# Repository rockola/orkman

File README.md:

# Orkman

[Runoffgroove Mockman](http://www.runoffgroove.com/mockman.html)

* v0.1 - 2020-04-08: initial version

## Description

From http://www.runoffgroove.com/mockman.html :

This circuit sounds uncannily reminiscent of the Rockman units from
the 1980s, minus the compression. Distortion is created by overdriving
the op-amps, similar to the Sansamp units. Adding the optional Red
LEDs will result in an even closer copy of the Rockman sound. When
including the LEDs, reduce the 470k resistors to avoid
over-distorting. You can also increase the 10k resistor for less
overdrive.

## License 

Mockman by runoffgroove.com is licensed under a Creative Commons
Attribution-NonCommercial-ShareAlike 3.0 Unported License.

## Images

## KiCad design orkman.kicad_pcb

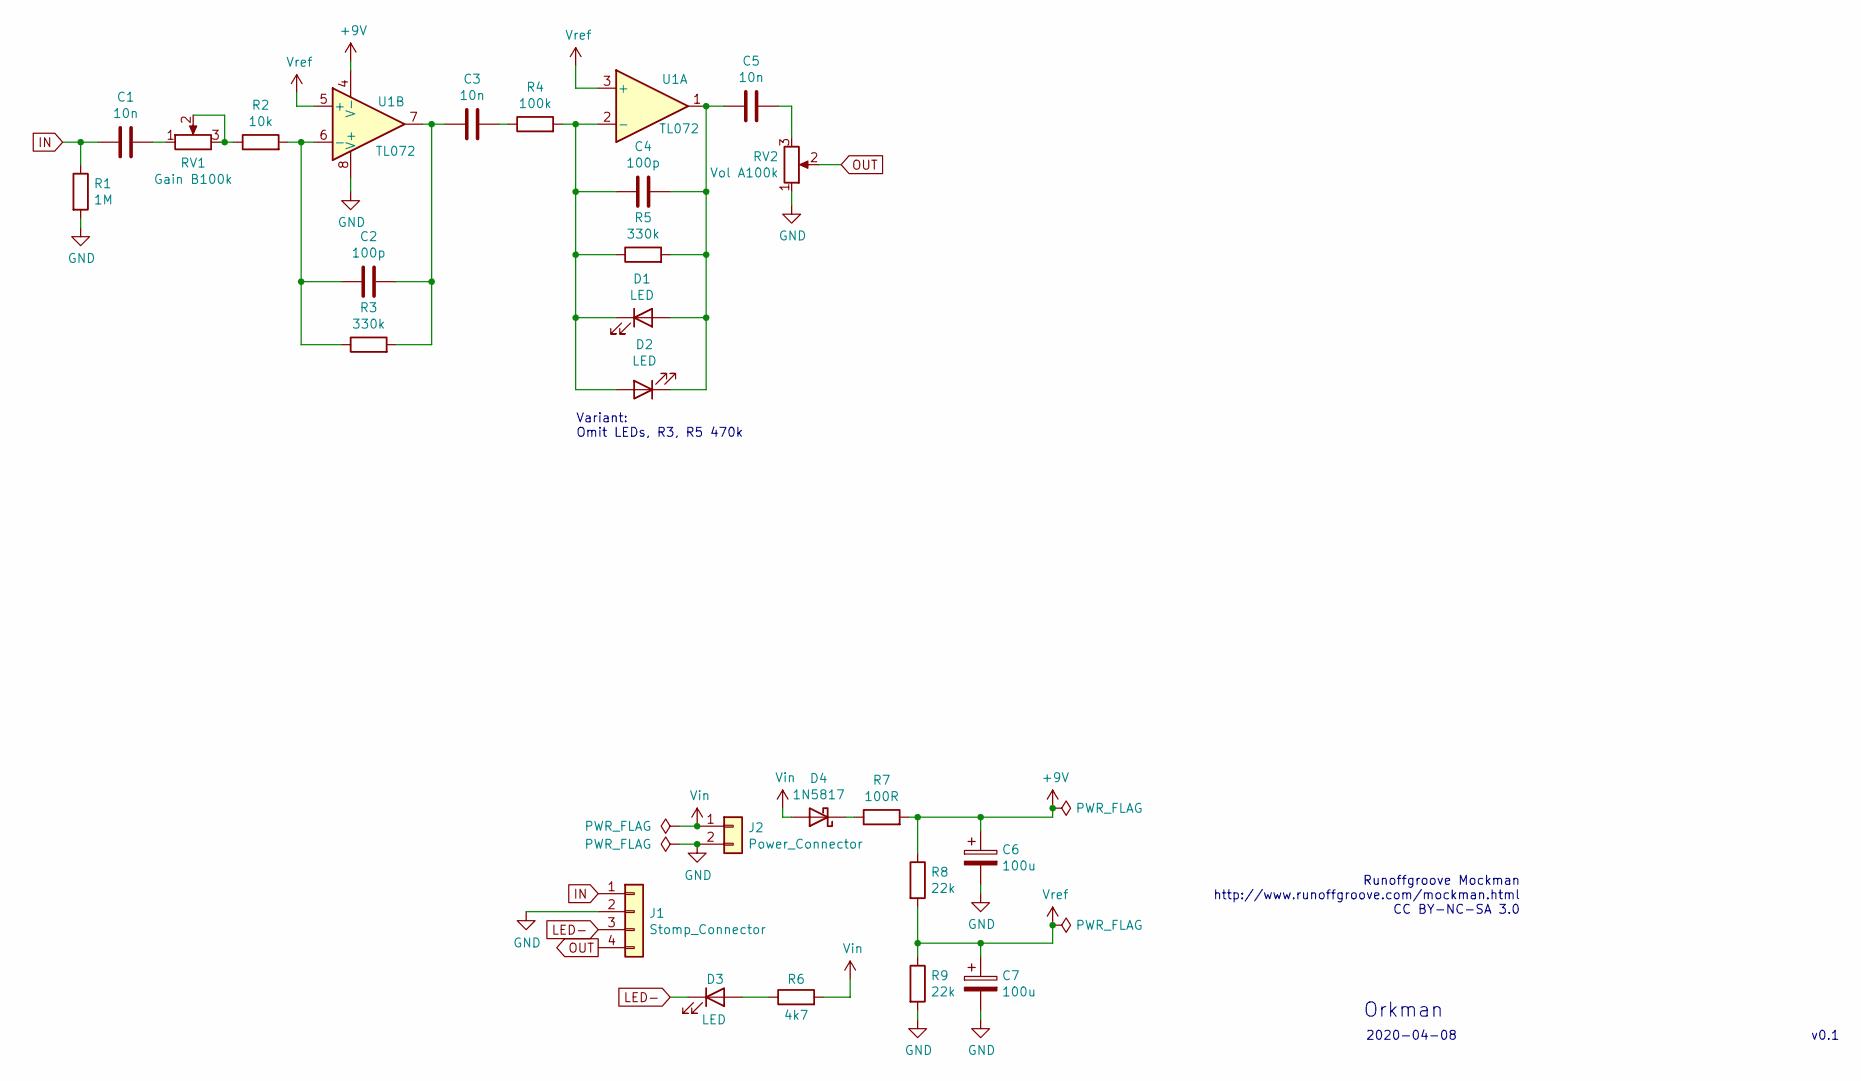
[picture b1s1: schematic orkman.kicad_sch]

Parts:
C1, C3, C5: 10n; C_Box_7.2_2.5
C2, C4: 100p; C_Box_7.2_2.5
C6, C7: 100u; CP_Radial_D6.3mm_P2.50mm
D1, D2, D3: LED; LED_D5.0mm
D4: 1N5817; D_DO-41_SOD81_P10.16mm_Horizontal
J1: Stomp_Connector; Stomp_4pin
J2: Power_Connector; Power_Header_2pin_TOP
R1: 1M; R_DIN0207
R2: 10k; R_DIN0207
R3, R5: 330k; R_DIN0207
R4: 100k; R_DIN0207
R6: 4k7; R_DIN0207
R7: 100R; R_DIN0207
R8, R9: 22k; R_DIN0207
RV1: Gain B100k; 9MM_PLASTIC_SHAFT
RV2: Vol A100k; 9MM_PLASTIC_SHAFT
U1: TL072; DIP-8_W7.62mm_Socket_LongPads

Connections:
+9V: C6.1, R7.2, R8.1, U1.4 (V-)
GND: C6.2, C7.2, J1.2 (GND), J2.2 (GND), R1.2, R9.2, RV2.1, U1.8 (V+)
IN: C1.1, J1.1 (IN), R1.1
LED-: D3.1 (K), J1.3 (SW)
unnamed: C1.2, RV1.1
unnamed: C2.1, R2.2, R3.1, U1.6 (-)
unnamed: C2.2, C3.1, R3.2, U1.7
unnamed: C3.2, R4.1
unnamed: C4.1, D1.1 (K), D2.2 (A), R4.2, R5.1, U1.2 (-)
unnamed: C4.2, C5.1, D1.2 (A), D2.1 (K), R5.2, U1.1
unnamed: C5.2, RV2.3
unnamed: D3.2 (A), R6.1
unnamed: D4.1 (K), R7.1
unnamed: R2.1, RV1.2, RV1.3
OUT: J1.4 (OUT), RV2.2
VIN: D4.2 (A), J2.1 (PWR), R6.2
VREF: C7.1, R8.2, R9.1, U1.3 (+), U1.5 (+)

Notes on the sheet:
Orkman
2020-04-08
Variant: Omit LEDs, R3, R5 470k
v0.1
Runoffgroove Mockman http://www.runoffgroove.com/mockman.html CC BY-NC-SA 3.0

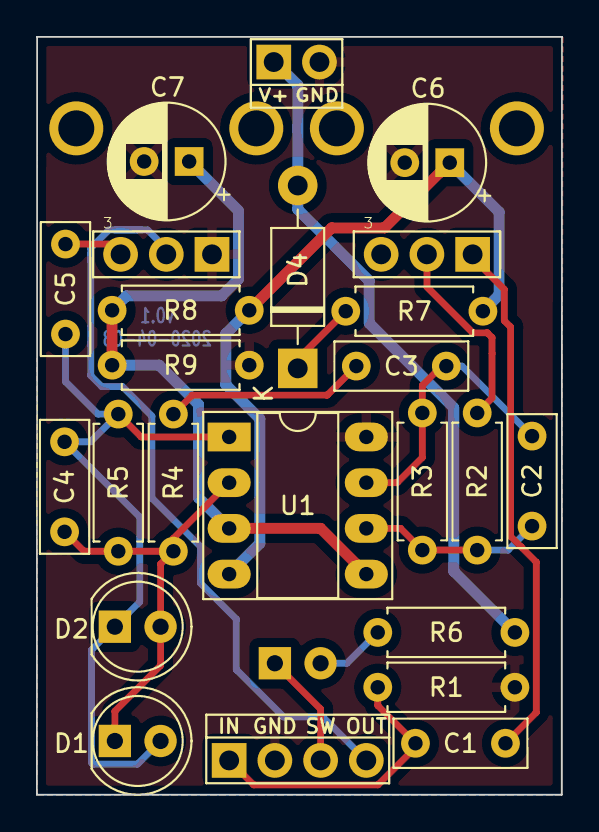
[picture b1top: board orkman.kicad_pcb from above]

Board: 2 copper layers, 29.2 x 42.1 mm, 25 parts (1 on the bottom side), 17 nets.

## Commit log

2020-04-08 v0.1: initial version
2020-04-08 PCB preview
2022-01-11 ignore backups directory
2022-01-11 updated to KiCad 6.0
